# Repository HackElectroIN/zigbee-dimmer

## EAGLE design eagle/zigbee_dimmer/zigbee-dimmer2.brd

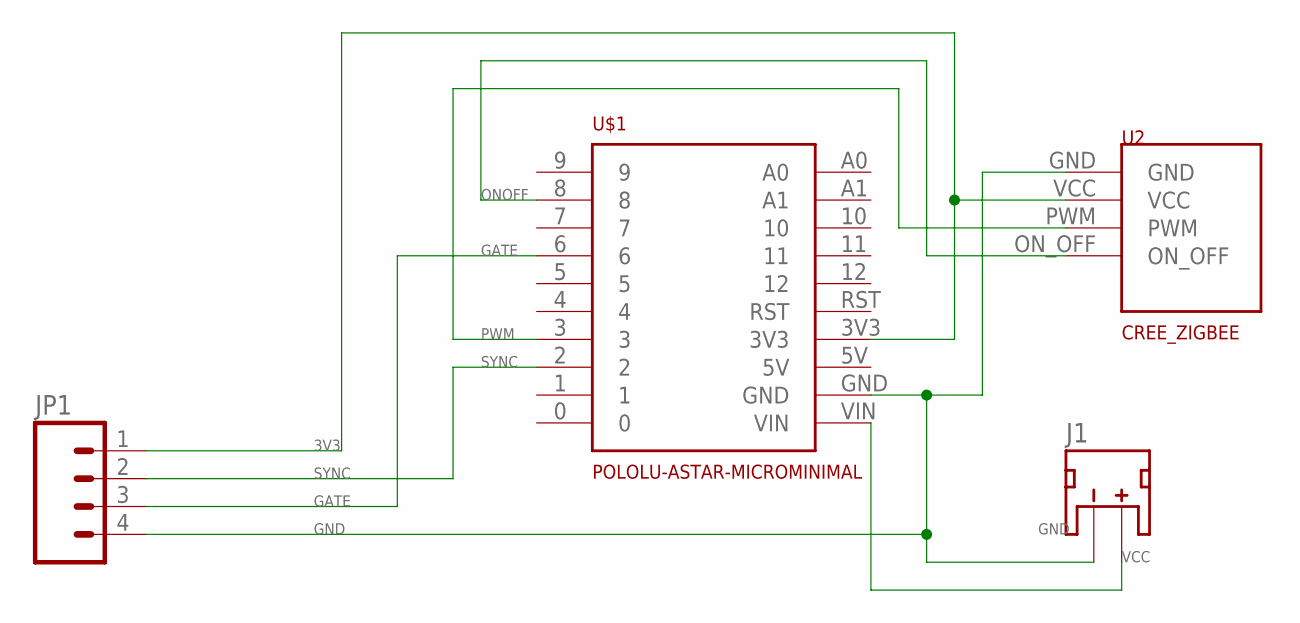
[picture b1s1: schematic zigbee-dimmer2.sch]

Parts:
J1: JST_2MM_MALE; JST-2-SMD
JP1: DIMMER_PINSSMD_180; 1X04-SMD
U2: CREE_ZIGBEE; CREE-ZIGBEE
U$1: POLOLU-ASTAR-MICROMINIMAL; POLOLU-ASTAR_MICRO_MIN

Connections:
3V3: JP1.1 (4), U2.VCC, U$1.3V3
5V: U$1.5V
GATE: JP1.3 (2), U$1.6
GND: J1.1 (-), JP1.4 (1), U2.GND, U$1.GND
ONOFF: U2.ON_OFF, U$1.8
PWM: U2.PWM, U$1.3
SYNC: JP1.2 (3), U$1.2
VCC: J1.2 (+), U$1.VIN

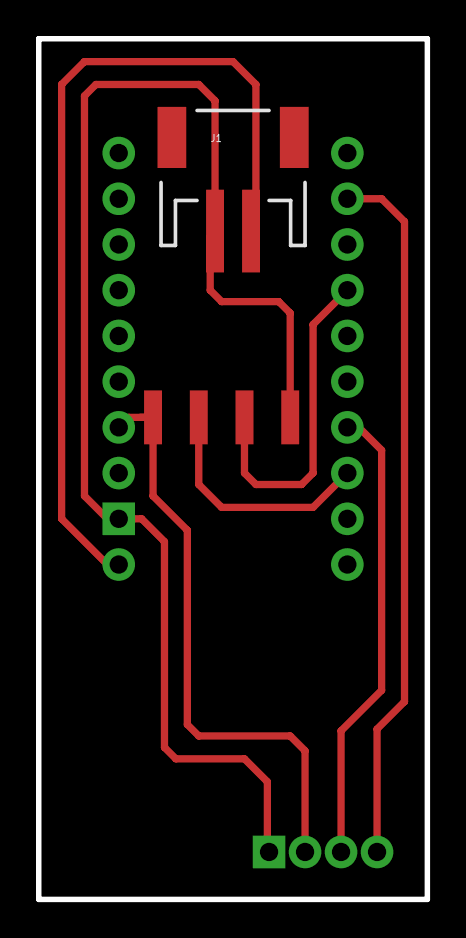
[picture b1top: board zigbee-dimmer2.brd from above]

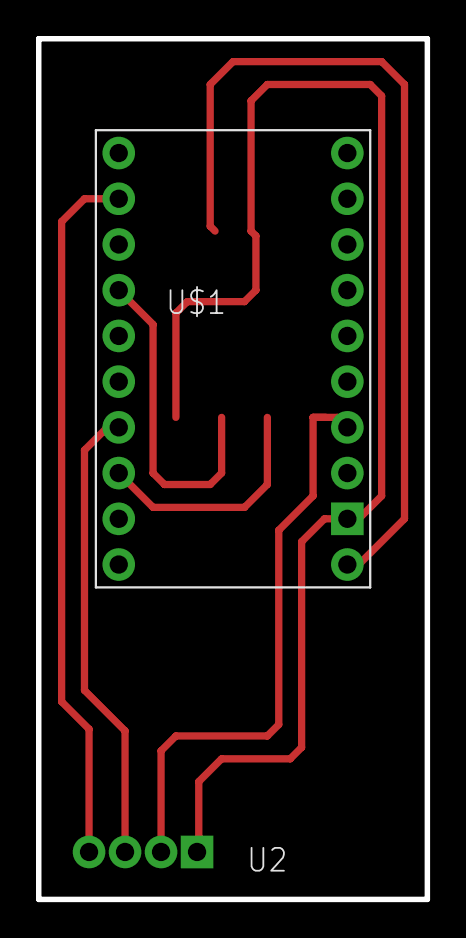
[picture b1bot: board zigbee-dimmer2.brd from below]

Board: 2 copper layers, 21.6 x 47.8 mm, 4 parts (2 on the bottom side), 7 nets.

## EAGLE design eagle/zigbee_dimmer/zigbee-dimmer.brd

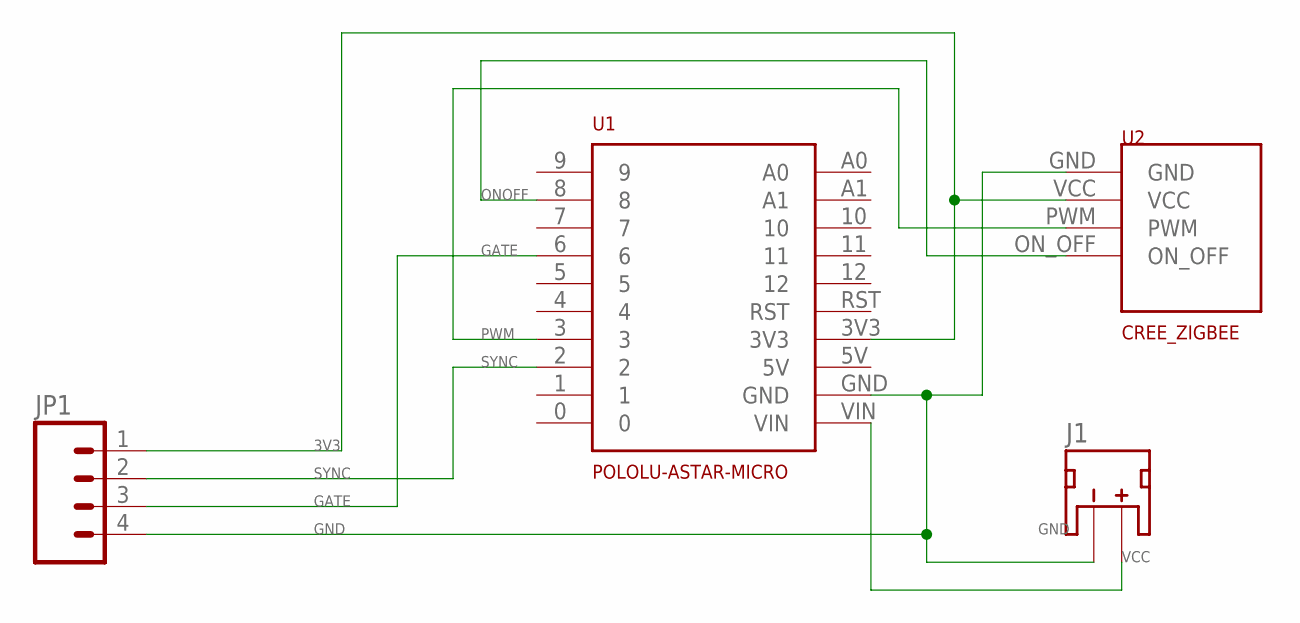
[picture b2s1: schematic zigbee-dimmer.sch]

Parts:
J1: JST_2MM_MALE; JST-2-SMD
JP1: DIMMER_PINSSMD_180; 1X04-SMD
U1: POLOLU-ASTAR-MICRO
U2: CREE_ZIGBEE; CREE-ZIGBEE

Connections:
3V3: JP1.1 (4), U1.3V3, U2.VCC
5V: U1.5V
GATE: JP1.3 (2), U1.6
GND: J1.1 (-), JP1.4 (1), U1.GND, U2.GND
ONOFF: U1.8, U2.ON_OFF
PWM: U1.3, U2.PWM
SYNC: JP1.2 (3), U1.2
VCC: J1.2 (+), U1.VIN

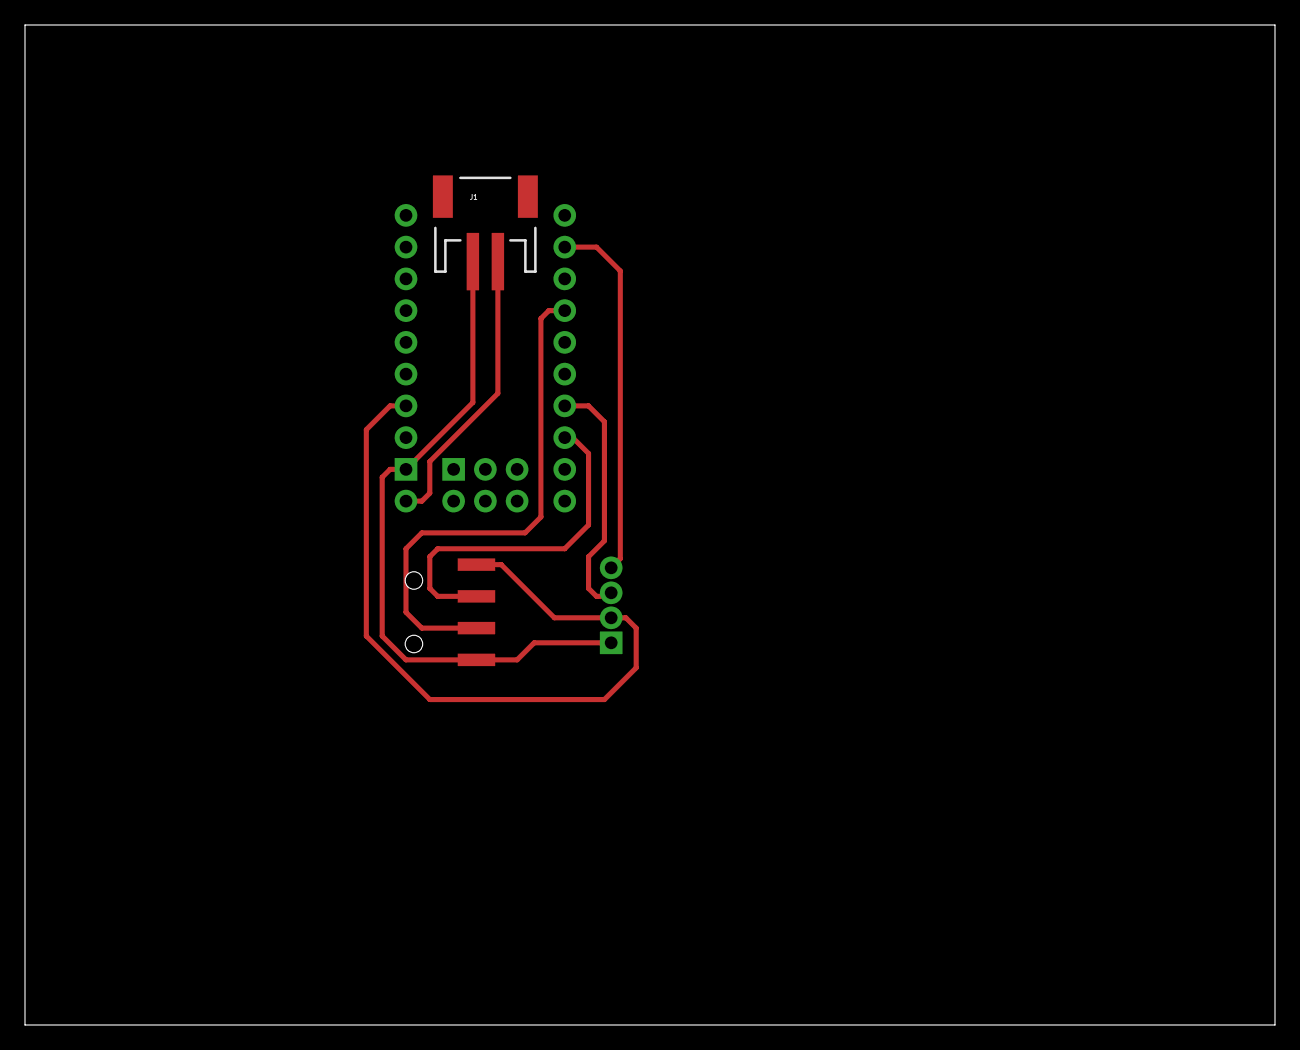
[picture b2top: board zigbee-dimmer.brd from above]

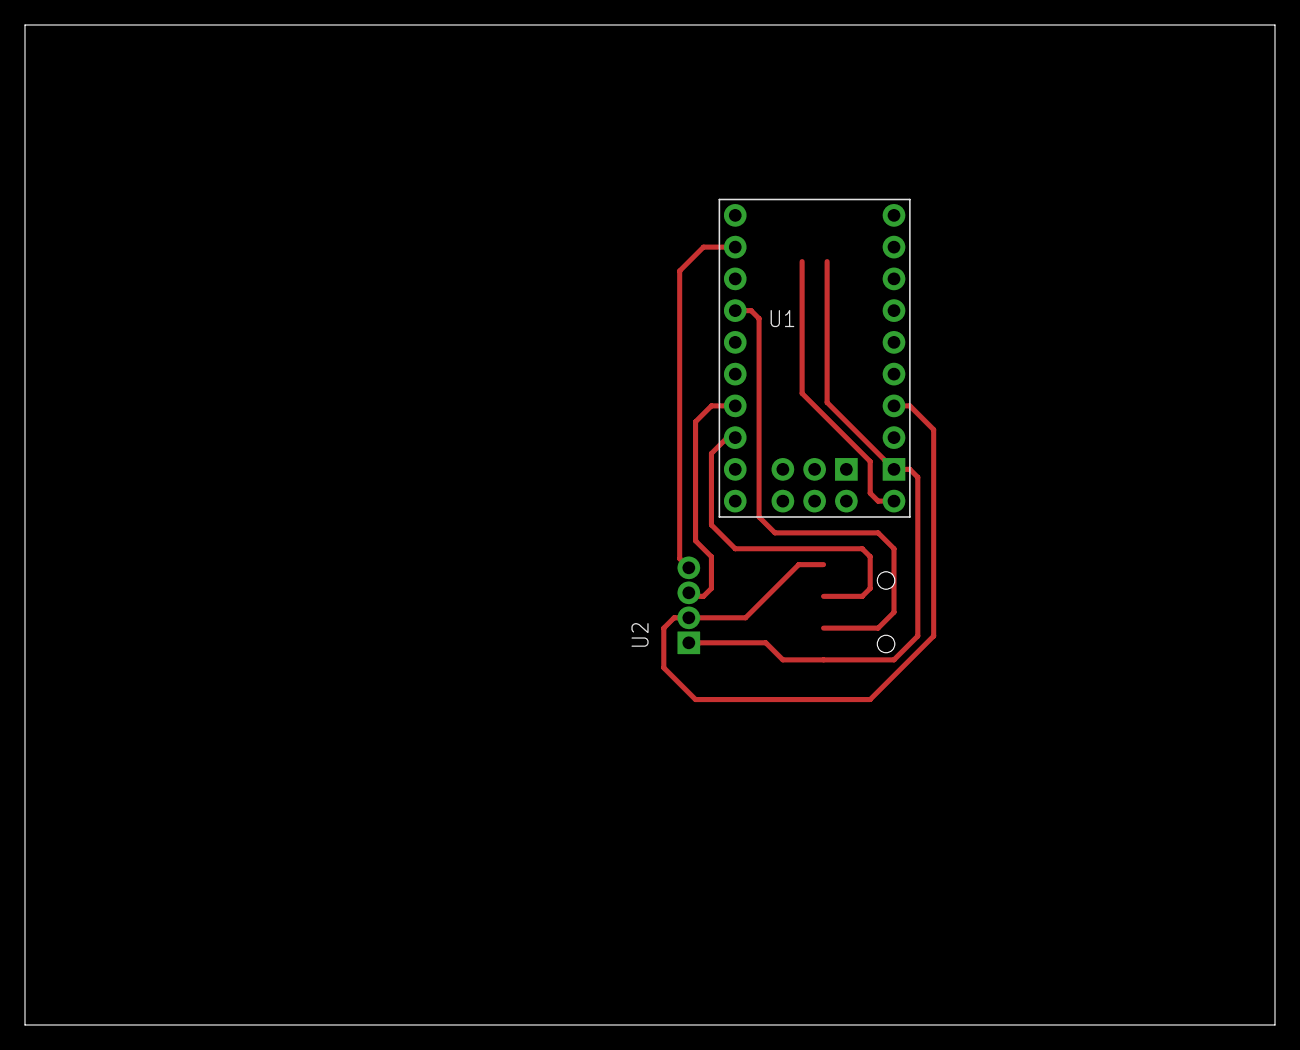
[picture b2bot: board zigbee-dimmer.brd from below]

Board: 2 copper layers, 100.0 x 80.0 mm, 4 parts (2 on the bottom side), 7 nets.

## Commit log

2017-01-06 Initial commit. Still messy
2017-01-07 Example that reads PWM form an external interrupt
2017-01-08 tests with external interrupts and regular pins
2017-01-08 putting everything together
2017-01-08 some cleanup
2017-01-08 Fixed flickering bug
2017-01-08 can't use trinket. Changing pinouts to match Uno and Mini
2017-01-09 Trying to use pin changes instead of external interrupts
2017-01-09 functions for testing pin change instead of external interrupts
2017-01-09 trying to handle flickering better
2017-01-09 flickering is mosetly gone
2017-01-11 copied updated code from the pin-change code
2017-01-11 some more cleanup
2017-01-14 some more attempts to fix flickering
2017-01-15 Handling flickering better?
2017-01-15 slightly better
2017-01-16 trying a new method. but still flickering on low (but doesn't BRIGHT up)
2017-01-16 more examples. fixed flickering?
2017-01-16 a few minor changes. better?
2017-01-19 cleanup
2017-01-21 started working on eagle libs
2017-01-22 Added ZigBee module
2017-01-28 eagle updated
2017-01-29 Smaller board design
2017-01-31 changes for board milling
2017-01-31 pcb stuff
2017-02-03 Code cleanup
2017-02-03 fixing first-on issue
    Whent he light turns on the first time, the CREE module doesn't give out
    PWM.
2017-02-03 Bugfix. LIghts are now on by default
2017-02-04 No need for the delay
2017-02-04 delay does seem to help
2017-03-14 No need for the AStar lib
2017-03-19 relocated milling files
2017-03-21 Updated comment re 50Hz

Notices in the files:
parts and their libraries:
SparkFun-Connectors: Licensing: Creative Commons ShareAlike 4.0 International - https://creativecommons.org/licenses/by-sa/4.0
